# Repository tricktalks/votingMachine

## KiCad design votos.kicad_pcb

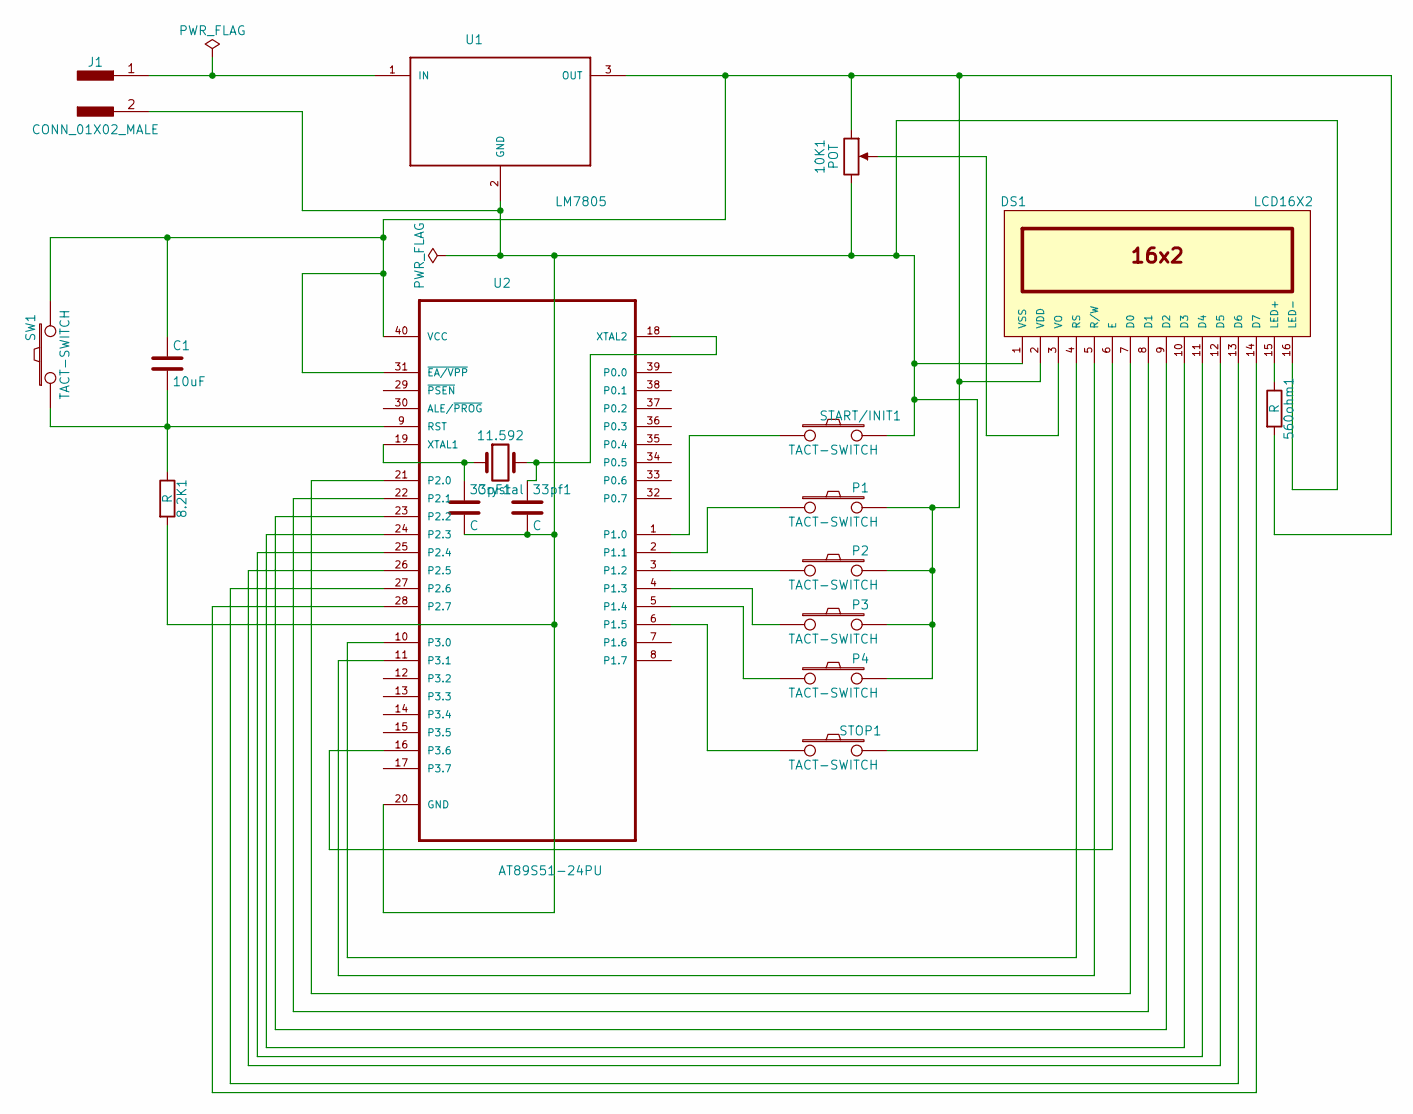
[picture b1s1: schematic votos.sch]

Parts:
8.2K1: R; R_Axial_DIN0204_L3.6mm_D1.6mm_P1.90mm_Vertical
10K1: POT; Potentiometer_Alps_RK09K_Horizontal
11.592: Crystal; Crystal_HC18-U_Vertical
33pF1, 33pf1: C; C_Axial_L3.8mm_D2.6mm_P7.50mm_Horizontal
560ohm1: R; R_Axial_DIN0204_L3.6mm_D1.6mm_P5.08mm_Vertical
C1: 10uF; C_Axial_L5.1mm_D3.1mm_P12.50mm_Horizontal
DS1: LCD16X2; WC1602A
J1: CONN_01X02_MALE; D_T-1_P2.54mm_Vertical_AnodeUp
P1, P2, P3, P4: TACT-SWITCH; SW_PUSH
START/INIT1: TACT-SWITCH; SW_PUSH
STOP1: TACT-SWITCH; SW_PUSH
SW1: TACT-SWITCH; SW_PUSH
U1: LM7805; TO220
U2: AT89S51-24PU; DIP254P1524X482-40

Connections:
unnamed: 8.2K1.1, C1.2, SW1.1, U2.9 (RST)
unnamed: 10K1.1, 560ohm1.2, C1.1, DS1.2 (VDD), P1.2, P2.2, P3.2, P4.2, SW1.2, U1.3 (OUT), U2.31 (~EA/VPP), U2.40 (VCC)
unnamed: 10K1.2, DS1.3 (VO)
unnamed: 8.2K1.2, 10K1.3, 33pF1.2, 33pf1.2, DS1.1 (VSS), DS1.16 (LED-), J1.2, START/INIT1.2, STOP1.2, U1.2 (GND), U2.20 (GND)
unnamed: 11.592.1, 33pF1.1, U2.19 (XTAL1)
unnamed: 11.592.2, 33pf1.1, U2.18 (XTAL2)
unnamed: 560ohm1.1, DS1.15 (LED+)
unnamed: DS1.4 (RS), U2.10 (P3.0)
unnamed: DS1.5 (R/W), U2.11 (P3.1)
unnamed: DS1.6 (E), U2.16 (P3.6)
unnamed: DS1.7 (D0), U2.21 (P2.0)
unnamed: DS1.8 (D1), U2.22 (P2.1)
unnamed: DS1.9 (D2), U2.23 (P2.2)
unnamed: DS1.10 (D3), U2.24 (P2.3)
unnamed: DS1.11 (D4), U2.25 (P2.4)
unnamed: DS1.12 (D5), U2.26 (P2.5)
unnamed: DS1.13 (D6), U2.27 (P2.6)
unnamed: DS1.14 (D7), U2.28 (P2.7)
unnamed: J1.1, U1.1 (IN)
unnamed: P1.1, U2.2 (P1.1)
unnamed: P2.1, U2.3 (P1.2)
unnamed: P3.1, U2.4 (P1.3)
unnamed: P4.1, U2.5 (P1.4)
unnamed: START/INIT1.1, U2.1 (P1.0)
unnamed: STOP1.1, U2.6 (P1.5)

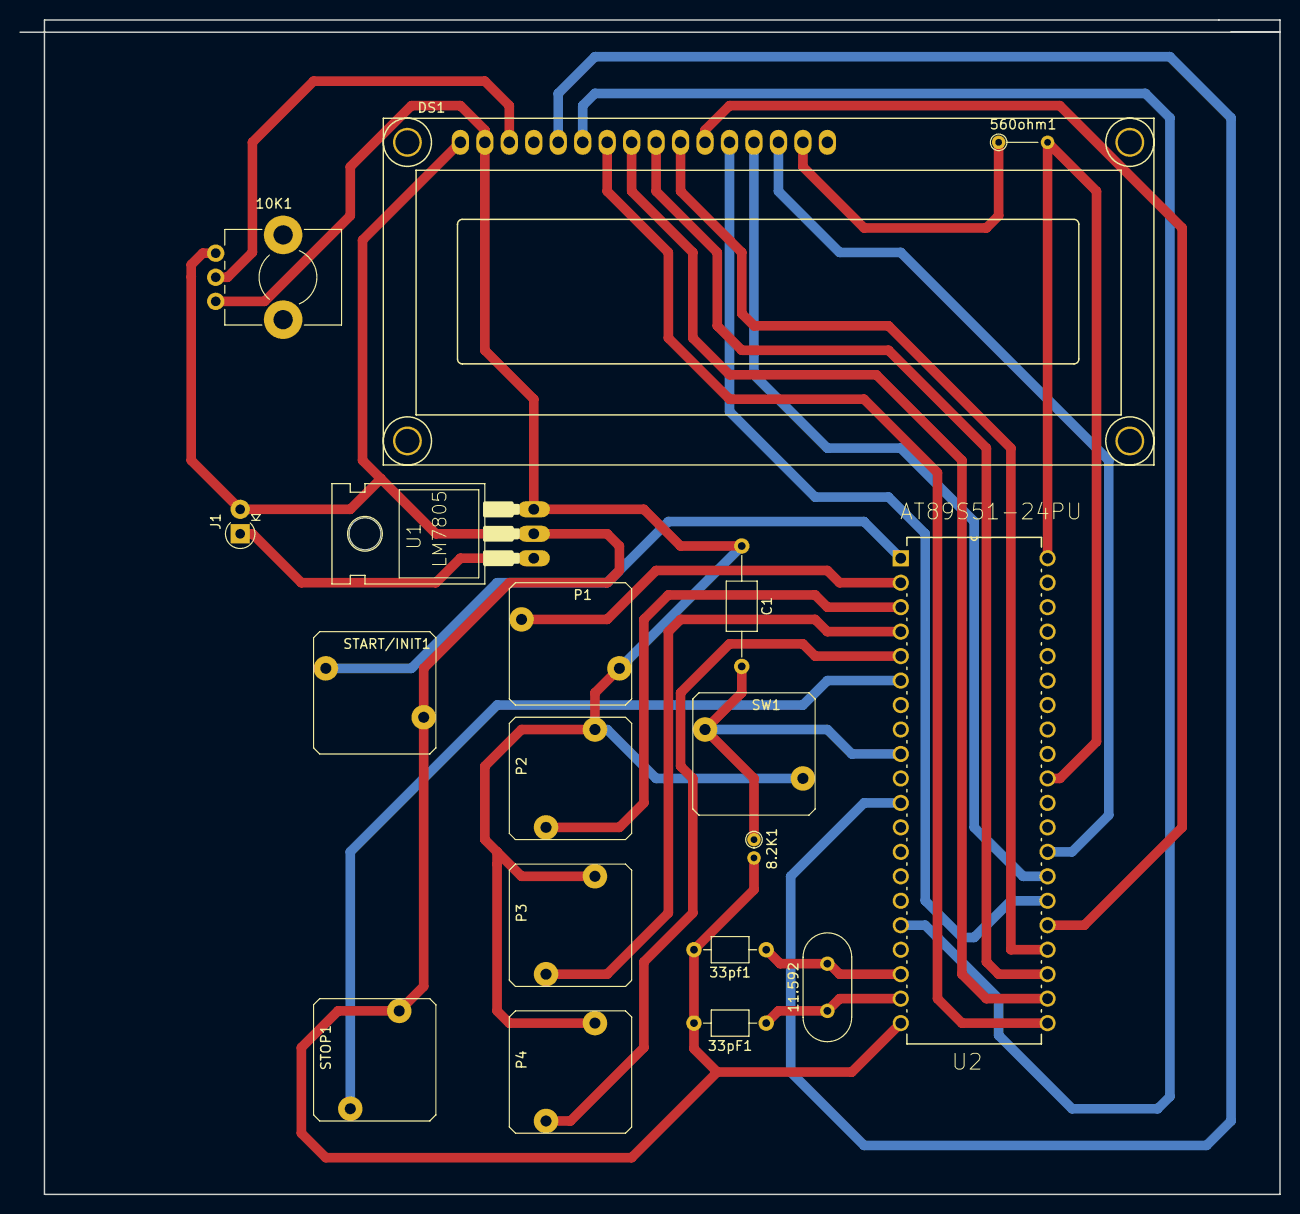
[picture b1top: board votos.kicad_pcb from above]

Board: 2 copper layers, 130.8 x 121.9 mm, 18 parts (0 on the bottom side), 25 nets.

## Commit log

2018-07-31 second commit
